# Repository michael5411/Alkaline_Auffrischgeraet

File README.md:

T

The circuits "pumps" 12V pulsed voltage into your 1.5 V alkaline batteryuntil a threshold voltage is reached. This process is controlled by a ESP32 microprocessor. In this case an ESP32 D1 mini is used. 

An Arduino sketch with one main-program and four subfunctions is available here. The project is based on home assistant. Home Assistant is necessary for the MQTT-comunication and as display for the whole process. 
You may kick out this part of the sketch and use it without MQTT-communication and home assistant integration.
Be sure to edit the WiFi and MQTT-credentials according to your needs.

KiCAD-schematic and a proven PCB-layout are provided,too.

Standard operation is like this:

- you insert up to 4 AA batteries
- the acccording LEDs begin to flash and you see on your Home Assistant dashboard, that it shows the actual voltage of your batteries.
- fresh up takes place and stops, as soon as 1.65 volts are reached for a least 10 times. You may go for another threshold voltage, if you like.

- Some really weak batteries will never show 1.65 volts, but they will be ok for appropriate use anyway.

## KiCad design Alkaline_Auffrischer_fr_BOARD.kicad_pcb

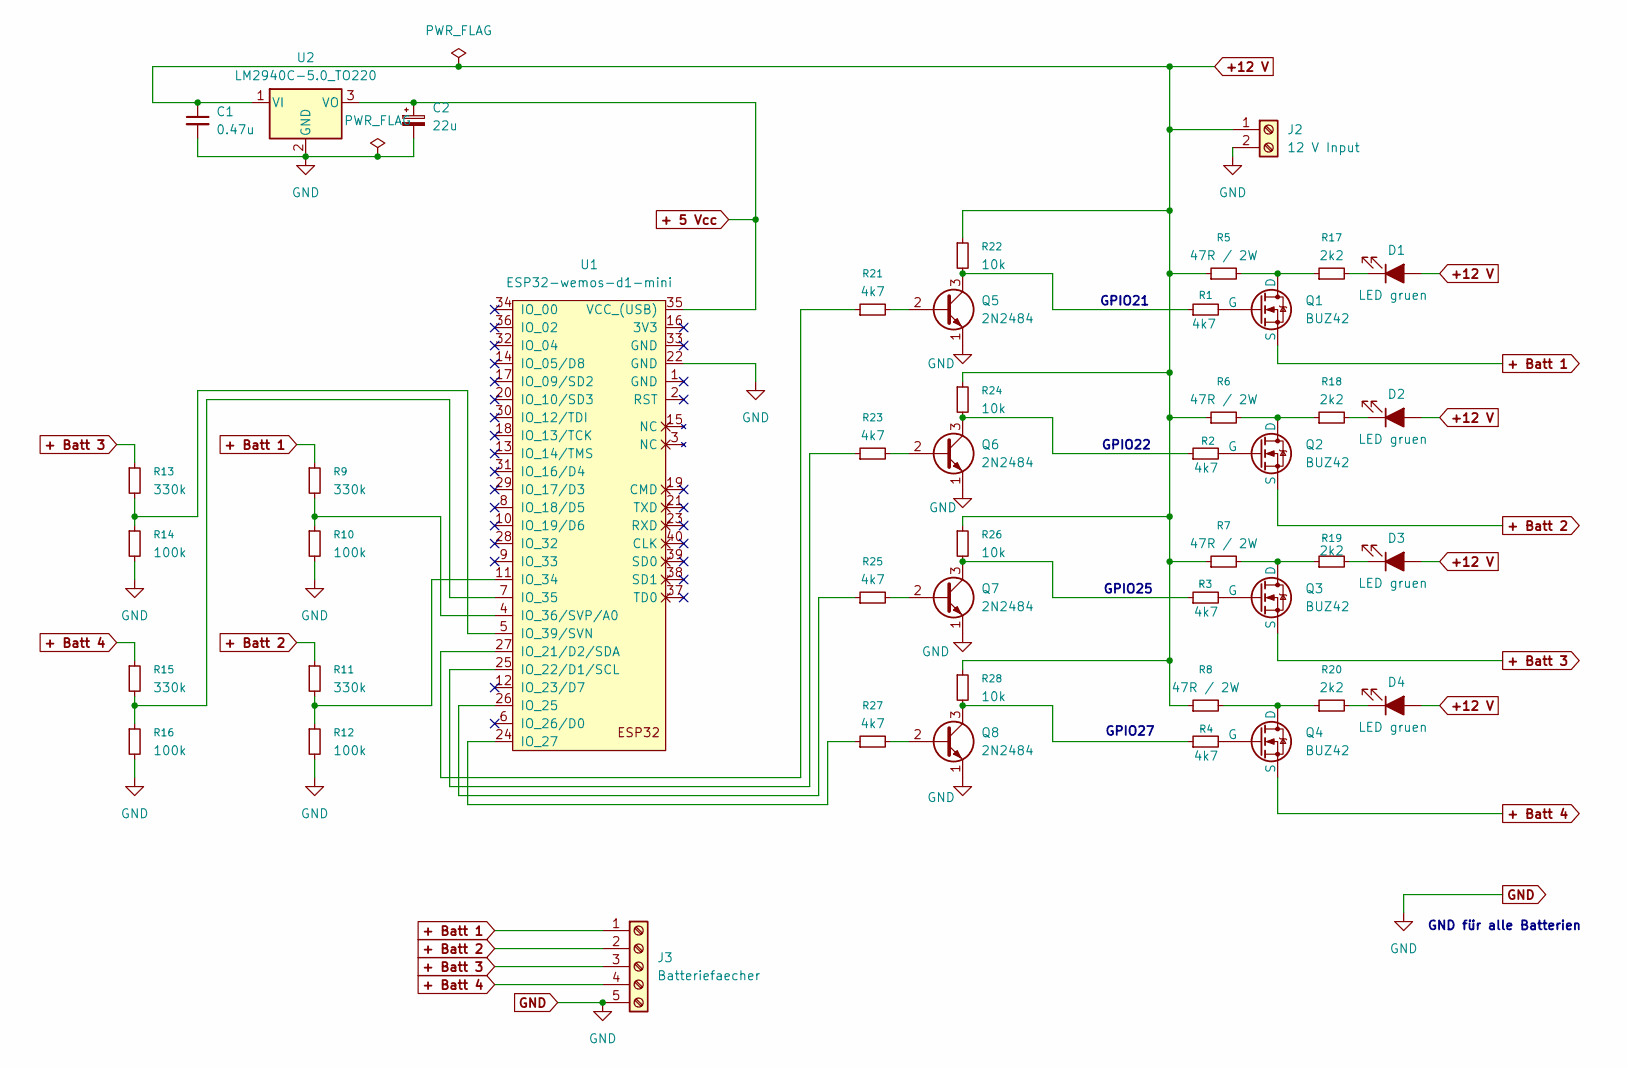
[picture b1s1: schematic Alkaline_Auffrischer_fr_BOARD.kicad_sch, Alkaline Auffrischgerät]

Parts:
C1: 0.47u; C_Axial_L3.8mm_D2.6mm_P7.50mm_Horizontal
C2: 22u; CP_Radial_D4.0mm_P1.50mm
D1, D2, D3, D4: LED gruen; LED_D5.0mm
J2: 12 V Input; TerminalBlock_MaiXu_MX126-5.0-02P_1x02_P5.00mm
J3: Batteriefaecher; TerminalBlock_MaiXu_MX126-5.0-05P_1x05_P5.00mm
Q1: BUZ42; TO-220-3_Vertical_1G2D3S
Q2, Q3, Q4: BUZ42
Q5, Q6, Q7, Q8: 2N2484; TO-18-3
R1, R2, R3, R4, R21, R23, R25, R27: 4k7; R_Axial_DIN0309_L9.0mm_D3.2mm_P12.70mm_Horizontal
R5, R6, R7, R8: 47R / 2W; R_Axial_DIN0414_L11.9mm_D4.5mm_P7.62mm_Vertical
R9, R11, R13, R15: 330k; R_Axial_DIN0309_L9.0mm_D3.2mm_P12.70mm_Horizontal
R10, R12, R14, R16: 100k; R_Axial_DIN0309_L9.0mm_D3.2mm_P12.70mm_Horizontal
R17, R18, R19, R20: 2k2; R_Axial_DIN0309_L9.0mm_D3.2mm_P12.70mm_Horizontal
R22, R24, R26, R28: 10k; R_Axial_DIN0309_L9.0mm_D3.2mm_P12.70mm_Horizontal
U1: ESP32-wemos-d1-mini; esp32-wemos-d1-mini
U2: LM2940C-5.0_TO220; TO-220F-3_Horizontal_TabDown

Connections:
+12 V: C1.1, D1.2 (A), D2.2 (A), D3.2 (A), D4.2 (A), J2.1, R5.1, R6.1, R7.1, R8.1, R22.1, R24.1, R26.1, R28.1, U2.1 (VI)
+ 5 Vcc: C2.1, U1.35 (VCC_(USB)), U2.3 (VO)
+ Batt 1: J3.1, Q1.3 (S), R9.1
+ Batt 2: J3.2, Q2.3 (S), R11.1
+ Batt 3: J3.3, Q3.3 (S), R13.1
+ Batt 4: J3.4, Q4.3 (S), R15.1
GND: C1.2, C2.2, J2.2, J3.5, Q5.1 (E), Q6.1 (E), Q7.1 (E), Q8.1 (E), R10.2, R12.2, R14.2, R16.2, U1.22 (GND), U2.2 (GND)
unnamed: D1.1 (K), R17.2
unnamed: D2.1 (K), R18.2
unnamed: D3.1 (K), R19.2
unnamed: D4.1 (K), R20.2
unnamed: Q1.2 (D), R5.2, R17.1
unnamed: Q1.1 (G), R1.2
unnamed: Q2.2 (D), R6.2, R18.1
unnamed: Q2.1 (G), R2.2
unnamed: Q3.2 (D), R7.2, R19.1
unnamed: Q3.1 (G), R3.2
unnamed: Q4.2 (D), R8.2, R20.1
unnamed: Q4.1 (G), R4.2
unnamed: Q5.2 (B), R21.2
unnamed: Q5.3 (C), R1.1, R22.2
unnamed: Q6.2 (B), R23.2
unnamed: Q6.3 (C), R2.1, R24.2
unnamed: Q7.2 (B), R25.2
unnamed: Q7.3 (C), R3.1, R26.2
unnamed: Q8.2 (B), R27.2
unnamed: Q8.3 (C), R4.1, R28.2
unnamed: R21.1, U1.27 (IO_21/D2/SDA)
unnamed: R23.1, U1.25 (IO_22/D1/SCL)
unnamed: R25.1, U1.26 (IO_25)
unnamed: R27.1, U1.24 (IO_27)
unnamed: R11.2, R12.1, U1.11 (IO_34)
unnamed: R15.2, R16.1, U1.7 (IO_35)
unnamed: R9.2, R10.1, U1.4 (IO_36/SVP/A0)
unnamed: R13.2, R14.1, U1.5 (IO_39/SVN)

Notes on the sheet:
GPIO22
GPIO27
GPIO21
GND für alle Batterien
GPIO25

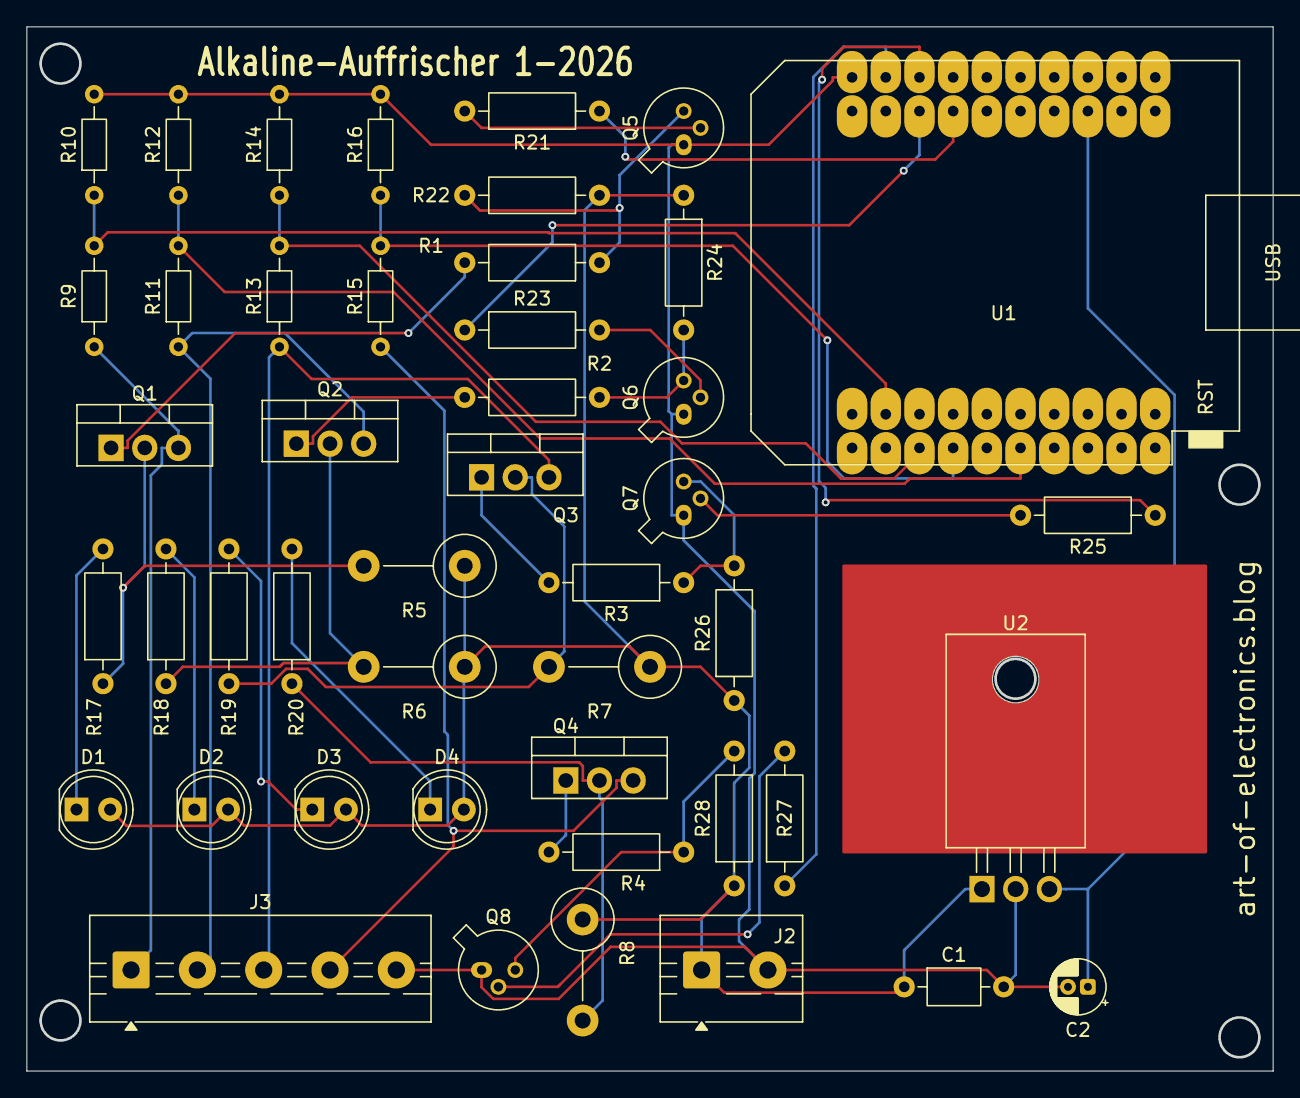
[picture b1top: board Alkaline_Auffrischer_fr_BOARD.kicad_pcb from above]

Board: 2 copper layers, 93.8 x 78.6 mm, 46 parts (0 on the bottom side), 35 nets.

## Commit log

2026-02-01 Add README content for battery management project
    Added project description and operational details for battery management system.
2026-02-01 Prototype
2026-02-01 Improve formatting in README.md
    Added additional spacing for clarity in the README.
2026-02-01 KiCAD 9.0.7 Files
2026-02-01 Arduino files C++
2026-02-09 Example for a MQTT-YAML in Home Assistant
    Please be sure to modify according to your MOSQUITTO-setup and topics.
